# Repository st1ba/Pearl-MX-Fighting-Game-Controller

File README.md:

# 🕹️ Pearl-MX Fighting Game Controller

Custom fighting game controller (leverless / arcade-style) built for precision inputs, low latency, and full customization.

---

## Overview

The **Pearl-MX Fighting Game Controller** is a custom-built controller designed for fighting games (Street Fighter, Tekken, Guilty Gear, etc.).  

## 🧠 Features

- Mechanical switch-based buttons (MX style)
- hitbox/leverless layout
- USB-C connection

---

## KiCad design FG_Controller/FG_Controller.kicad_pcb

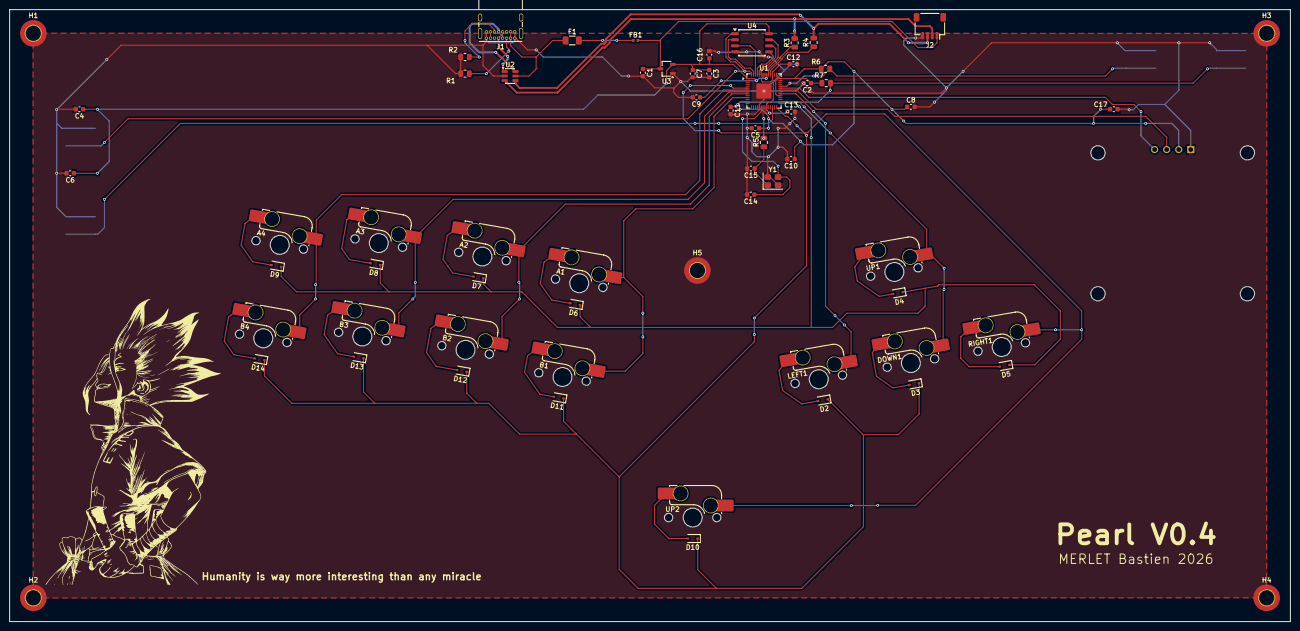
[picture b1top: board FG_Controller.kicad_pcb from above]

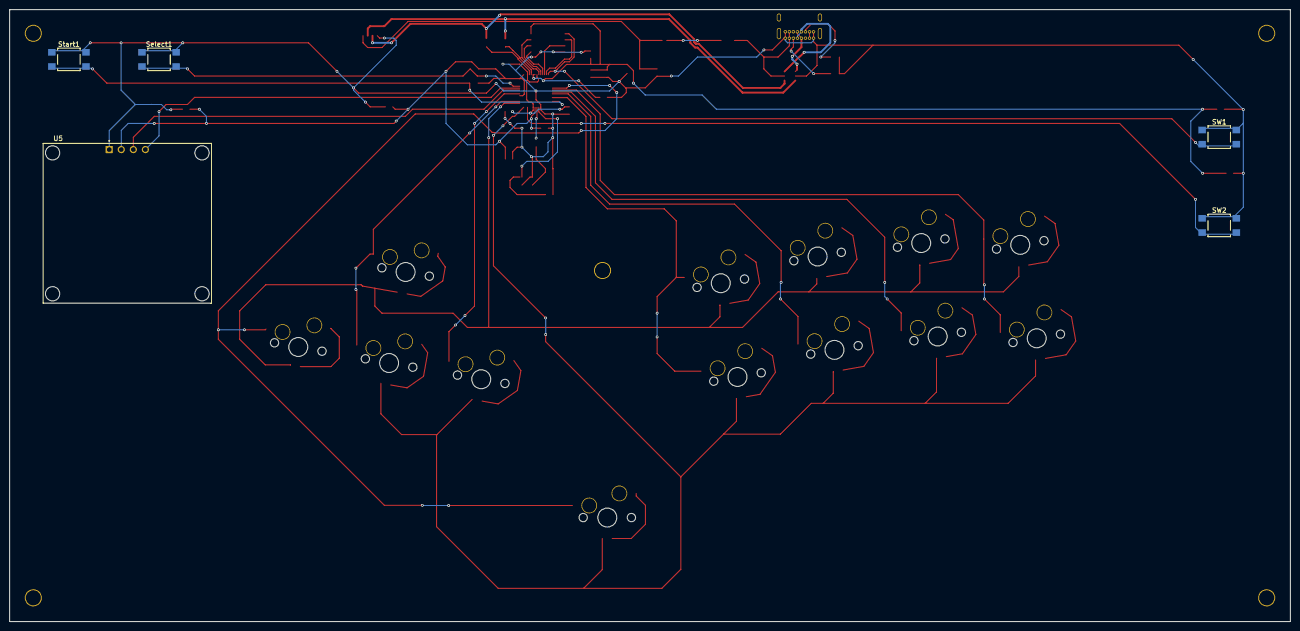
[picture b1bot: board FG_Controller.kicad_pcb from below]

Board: 2 copper layers, 270.0 x 129.0 mm, 70 parts (5 on the bottom side), 50 nets.

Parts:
A1, A2, A3, A4: MX_SW_HS; SW_MX_HS_CPG151101S11_1u
B1, B2, B3, B4: MX_SW_HS; SW_MX_HS_CPG151101S11_1u
C1, C2, C3, C11, C16: 1u; C_0603_1608Metric
C4, C5, C6, C7, C8, C9, C10, C12, C13: 100n; C_0603_1608Metric
C14, C15: 30p; C_0603_1608Metric
C17: C; C_0603_1608Metric
D2, D3, D4, D5, D6, D7, D8, D9, D10, D11, D12, D13, D14: 1N4001; D_SOD-323
DOWN1: MX_SW_HS; SW_MX_HS_CPG151101S11_1u
F1: 1A; Fuse_1206_3216Metric
FB1: 100 oHM 100 MHz; L_0402_1005Metric
H1, H2, H3, H4, H5: MountingHole_Pad; MountingHole_3.2mm_M3_DIN965_Pad_TopOnly
Humanity is way more interesting than any miracle: LOGO
J1: USB_C_Receptacle_USB2.0_16P; USB_C_Receptacle_GCT_USB4085
J2: JST- 1.00mm 4 Pin; JST_SH_SM04B-SRSS-TB_1x04-1MP_P1.00mm_Horizontal
LEFT1: MX_SW_HS; SW_MX_HS_CPG151101S11_1u
R1, R2: 5100; R_0805_2012Metric
R3, R4: 22; R_0805_2012Metric
R5: 1000; R_0805_2012Metric
R6, R7: 1k; R_0805_2012Metric
RIGHT1: MX_SW_HS; SW_MX_HS_CPG151101S11_1u
SW1, SW2: SW_Push; SW_SPST_TL3305A
Select1: SW_Push; SW_SPST_TL3305A
Start1: SW_Push; SW_SPST_TL3305A
U1: RP2040; QFN-56-1EP_7x7mm_P0.4mm_EP3.2x3.2mm
U2: USBLC6-2SC6; SOT-23-6
U3: AP2127N3-1.2; TSOT-23
U4: W25Q16JVSS; SOIC-8_5.3x5.3mm_P1.27mm
U5: ER_OLEDM0.91_1x-I2C; LCD_OLED_128X64_1.3_I2C
UP1, UP2: MX_SW_HS; SW_MX_HS_CPG151101S11_1u
Y1: 12MHz Crystal 3225; Crystal_SMD_3225-4Pin_3.2x2.5mm

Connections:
+1V1: C11.1, C12.1, C13.1, U1.23 (DVDD), U1.45 (VREG_VOUT), U1.50 (DVDD)
+3V3: C2.1, C3.1, C4.1, C5.1, C6.1, C7.1, C8.1, C9.1, C10.1, C16.1, C17.1, R6.2, R7.1, U1.1 (IOVDD), U1.10 (IOVDD), U1.22 (IOVDD), U1.33 (IOVDD), U1.42 (IOVDD), U1.43 (ADC_AVDD), U1.44 (VREG_VIN), U1.48 (USB_VDD), U1.49 (IOVDD), U3.2 (VO), U4.8 (VCC), U5.2 (VCC)
/<NO NET>: J1.A6 (D+), U2.6 (I/O1)
/CS_: SW1.2, U1.56 (~QSPI_SS), U4.1 (~CS)
/DN: J2.2, R3.2, U2.3 (I/O2)
/DP: J2.3, R4.2, U2.4 (I/O2)
/RUN_: SW2.2, U1.26 (RUN)
/SCLK_: U1.52 (QSPI_SCLK), U4.6 (CLK)
/SD0_: U1.53 (QSPI_SD0), U4.5 (DI/IO_{0})
/SD1_: U1.55 (QSPI_SD1), U4.2 (DO/IO_{1})
/SD2_: U1.54 (QSPI_SD2), U4.3 (~WP/IO_{2})
/SD3_: U1.51 (QSPI_SD3), U4.7 (~HOLD/~RESET/IO_{3})
/VBUS: F1.1, J1.A4 (VBUS), J1.A9 (VBUS), J1.B4 (VBUS), J1.B9 (VBUS), U2.5 (VBUS)
/Vfused_: C1.1, FB1.2, J2.1, U3.3 (VI)
/XIN-: C14.1, U1.20 (XIN), Y1.3
/XOUT_: C15.1, R5.1, Y1.1
/d1-: J1.A7 (D-), J1.B7 (D-), U2.1 (I/O1)
GND: C1.2, C2.2, C3.2, C4.2, C5.2, C6.2, C7.2, C8.2, C9.2, C10.2, C11.2, C12.2, C13.2, C14.2, C15.2, C16.2, C17.2, H1.1 (1_1), H2.1 (1_1), H3.1 (1_1), H4.1 (1_1), H5.1 (1_1), J1.A1 (GND), J1.A12 (GND), J1.B1 (GND), J1.B12 (GND), J2.4, R1.2, R2.2, SW1.1, SW2.1, Select1.1, Start1.1, U1.19 (TESTEN), U1.57 (GND), U2.2 (GND), U3.1 (GND), U4.4 (GND), U5.1 (GND), Y1.2, Y1.4
GP4: RIGHT1.1, U1.6 (GPIO4), UP2.1
GP5: A4.1, B4.1, U1.7 (GPIO5)
GP6: A3.1, B3.1, U1.8 (GPIO6)
GP7: A2.1, B2.1, U1.9 (GPIO7)
GP8: A1.1, B1.1, U1.11 (GPIO8)
GP10: R7.2, Start1.2, U1.13 (GPIO10)
GP17: D2.1 (K), D3.1 (K), D10.1 (K), D11.1 (K), D12.1 (K), D13.1 (K), D14.1 (K), U1.28 (GPIO17)
GP18: D4.1 (K), D5.1 (K), D6.1 (K), D7.1 (K), D8.1 (K), D9.1 (K), U1.29 (GPIO18)
GP19: DOWN1.1, U1.30 (GPIO19), UP1.1
GP22: LEFT1.1, U1.34 (GPIO22)
GP24: U1.36 (GPIO24), U5.3 (SCL)
GP25: U1.37 (GPIO25), U5.4 (SDA)
GP26: R6.1, Select1.2, U1.38 (GPIO26/ADC0)
unnamed: D2.2 (A), LEFT1.2
unnamed: D3.2 (A), DOWN1.2
unnamed: D4.2 (A), UP1.2
unnamed: D5.2 (A), RIGHT1.2
unnamed: A1.2, D6.2 (A)
unnamed: A2.2, D7.2 (A)
unnamed: A3.2, D8.2 (A)
unnamed: A4.2, D9.2 (A)
unnamed: D10.2 (A), UP2.2
unnamed: B1.2, D11.2 (A)
unnamed: B2.2, D12.2 (A)
unnamed: B3.2, D13.2 (A)
unnamed: B4.2, D14.2 (A)
unnamed: F1.2, FB1.1
unnamed: J1.A5 (CC1), R1.1
unnamed: J1.B5 (CC2), R2.1
unnamed: R4.1, U1.46 (USB_DM)
unnamed: R3.1, U1.47 (USB_DP)
unnamed: R5.2, U1.21 (XOUT)

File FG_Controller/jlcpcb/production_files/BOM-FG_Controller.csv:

Comment,Designator,Footprint,LCSC,Quantity
12MHz Crystal 3225,Y1,Crystal_SMD_3225-4Pin_3.2x2.5mm,C9002,1
MX_SW_HS,A3,SW_MX_HS_CPG151101S11_1u,,1
1N4001,D12,D_SOD-323,,1
1N4001,D7,D_SOD-323,,1
RP2040,U1,QFN-56-1EP_7x7mm_P0.4mm_EP3.2x3.2mm,,1
MX_SW_HS,DOWN1,SW_MX_HS_CPG151101S11_1u,,1
USBLC6-2SC6,U2,SOT-23-6,,1
W25Q16JVSS,U4,SOIC-8_5.3x5.3mm_P1.27mm,,1
1u,C16,C_0603_1608Metric,,1
5100,R2,R_0805_2012Metric,,1
1000,R5,R_0805_2012Metric,,1
1N4001,D5,D_SOD-323,,1
1A,F1,Fuse_1206_3216Metric,,1
100 oHM 100 MHz,FB1,L_0402_1005Metric,,1
1N4001,D4,D_SOD-323,,1
MX_SW_HS,B2,SW_MX_HS_CPG151101S11_1u,,1
100n,C4,C_0603_1608Metric,,1
MX_SW_HS,B1,SW_MX_HS_CPG151101S11_1u,,1
100n,C6,C_0603_1608Metric,,1
MX_SW_HS,RIGHT1,SW_MX_HS_CPG151101S11_1u,,1
1N4001,D6,D_SOD-323,,1
30p,C14,C_0603_1608Metric,,1
1u,C2,C_0603_1608Metric,,1
1N4001,D3,D_SOD-323,,1
MX_SW_HS,B3,SW_MX_HS_CPG151101S11_1u,,1
MX_SW_HS,A1,SW_MX_HS_CPG151101S11_1u,,1
22,R4,R_0805_2012Metric,,1
1u,C11,C_0603_1608Metric,,1
USB_C_Receptacle_USB2.0_16P,J1,USB_C_Receptacle_GCT_USB4085,,1
22,R3,R_0805_2012Metric,,1
MX_SW_HS,B4,SW_MX_HS_CPG151101S11_1u,,1
100n,C9,C_0603_1608Metric,,1
100n,C13,C_0603_1608Metric,,1
MX_SW_HS,A4,SW_MX_HS_CPG151101S11_1u,,1
1u,C1,C_0603_1608Metric,,1
MX_SW_HS,UP2,SW_MX_HS_CPG151101S11_1u,,1
1u,C3,C_0603_1608Metric,,1
1N4001,D9,D_SOD-323,,1
MX_SW_HS,LEFT1,SW_MX_HS_CPG151101S11_1u,,1
JST- 1.00mm 4 Pin,J2,JST_SH_SM04B-SRSS-TB_1x04-1MP_P1.00mm_Horizontal,,1
100n,C7,C_0603_1608Metric,,1
C,C17,C_0603_1608Metric,,1
5100,R1,R_0805_2012Metric,,1
1N4001,D2,D_SOD-323,,1
100n,C8,C_0603_1608Metric,,1
100n,C5,C_0603_1608Metric,,1
1k,R7,R_0805_2012Metric,,1
30p,C15,C_0603_1608Metric,,1
MX_SW_HS,UP1,SW_MX_HS_CPG151101S11_1u,,1
100n,C12,C_0603_1608Metric,,1
1N4001,D10,D_SOD-323,,1
1N4001,D13,D_SOD-323,,1
MX_SW_HS,A2,SW_MX_HS_CPG151101S11_1u,,1
1k,R6,R_0805_2012Metric,,1
AP2127N3-1.2,U3,TSOT-23,,1
1N4001,D8,D_SOD-323,,1
1N4001,D11,D_SOD-323,,1
100n,C10,C_0603_1608Metric,,1
1N4001,D14,D_SOD-323,,1
SW_Push,SW1,SW_SPST_TL3305A,,1
ER_OLEDM0.91_1x-I2C,U5,LCD_OLED_128X64_1.3_I2C,,1
SW_Push,Start1,SW_SPST_TL3305A,,1
SW_Push,SW2,SW_SPST_TL3305A,,1
SW_Push,Select1,SW_SPST_TL3305A,,1

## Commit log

2026-04-10 First Upload
2026-04-14 Update PCB 0.5 + Casing step files
